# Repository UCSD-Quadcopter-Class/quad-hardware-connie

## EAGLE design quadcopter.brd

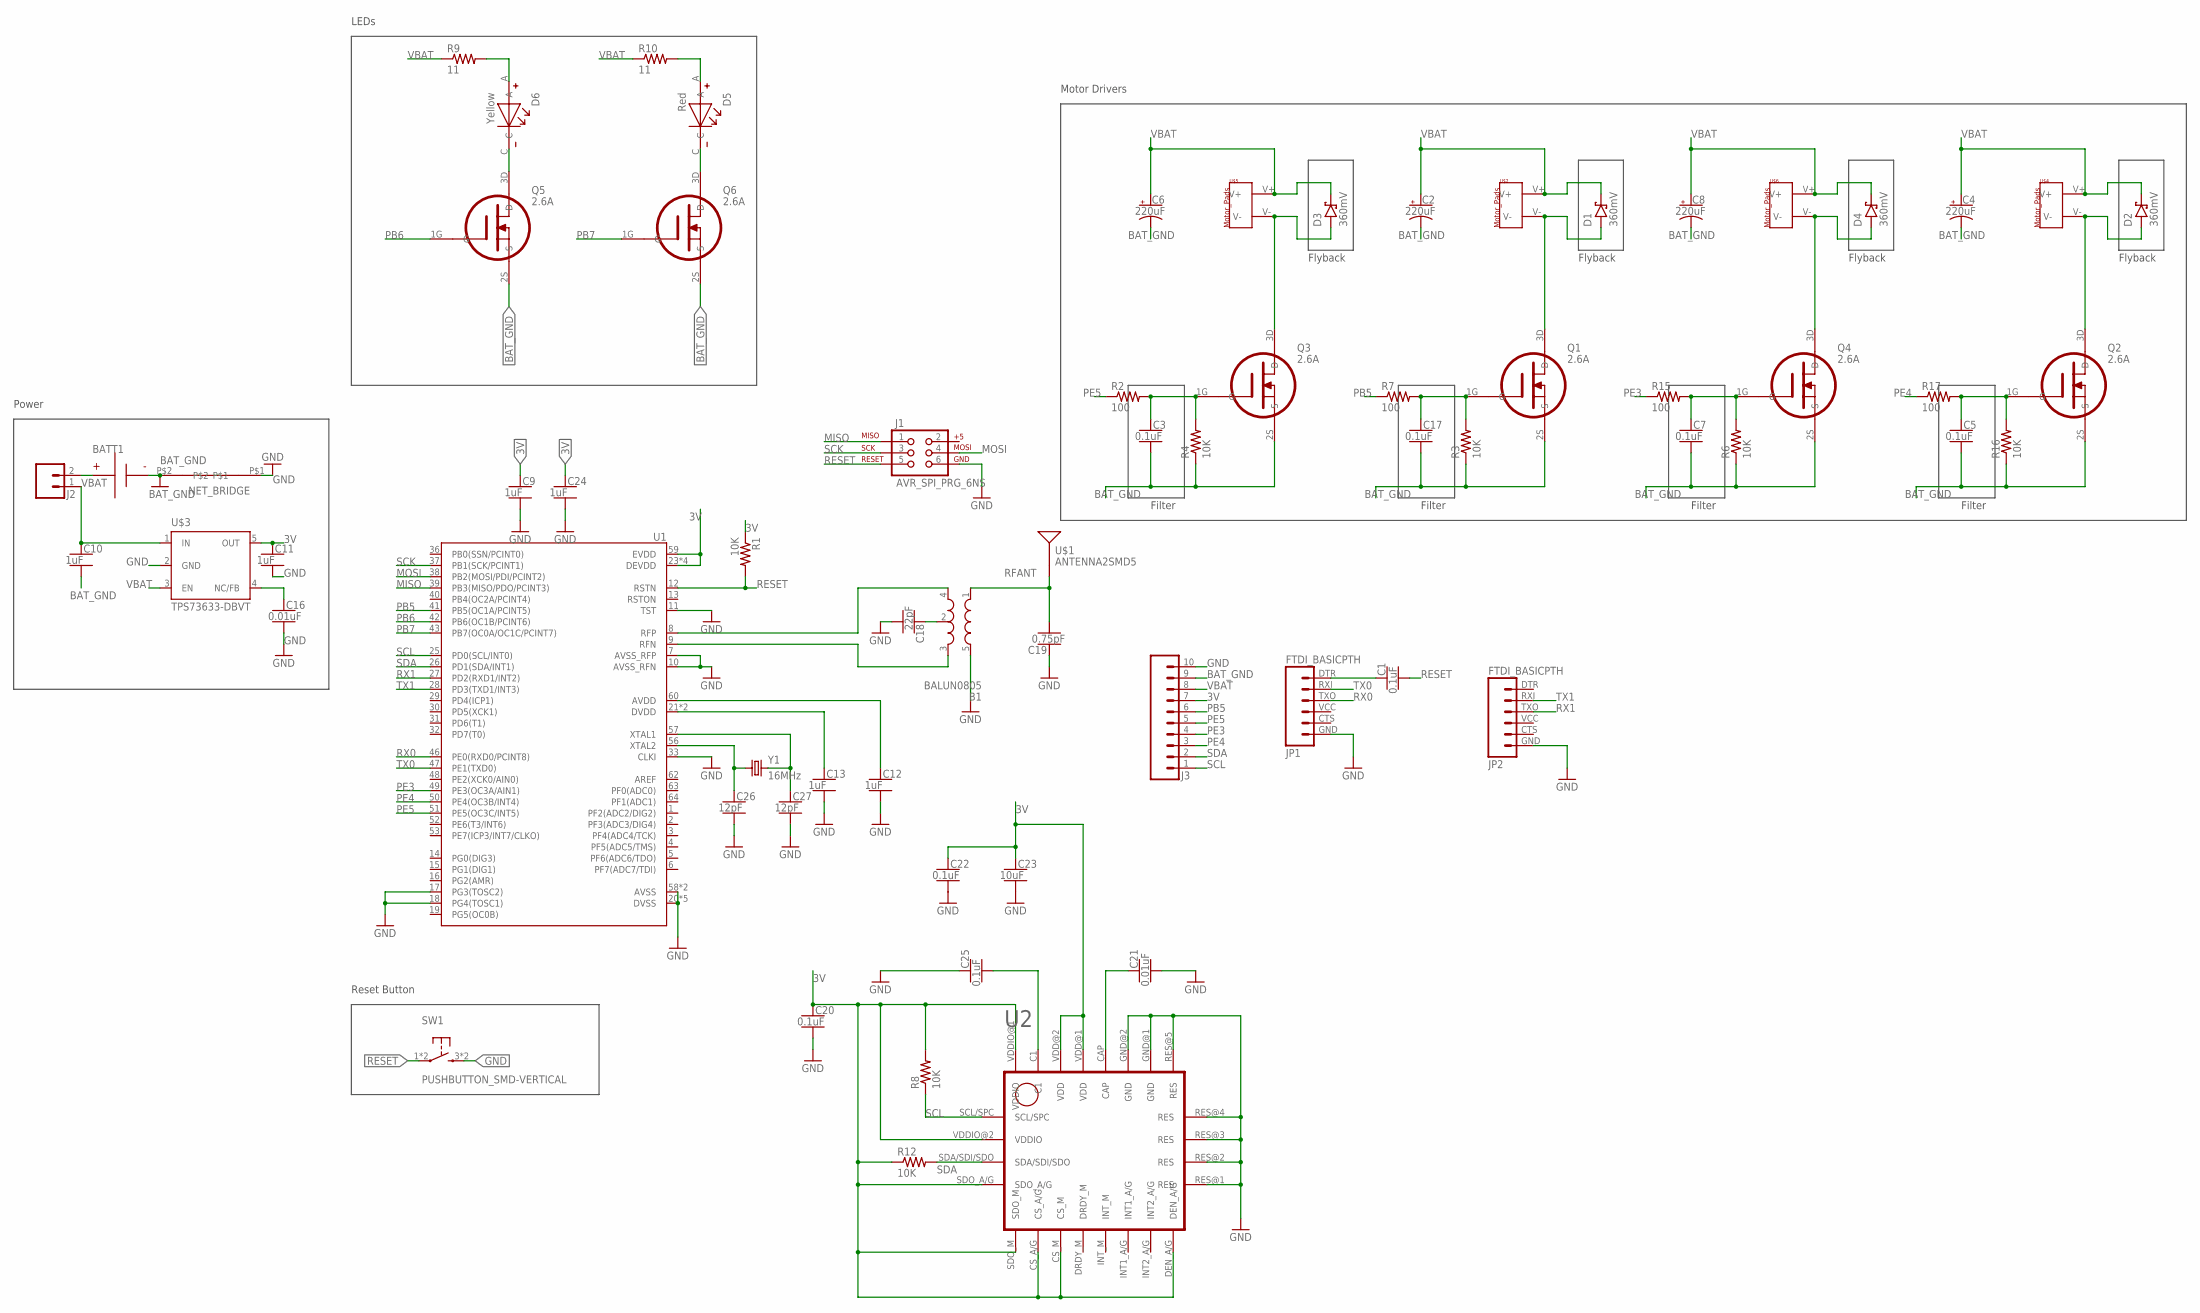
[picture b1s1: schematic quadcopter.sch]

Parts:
B1: BALUN0805; BALUN
BATT1: BATTERY-HUBSAN-W/HOLDER; BATTERY-W/HOLDER-380MAH-HUBSAN
C1: 0.1uF; CERAMIC_CAP_0805
C2, C4, C6, C8: 220uF; CAPMP7343X310_HS
C3, C5, C7, C17, C20, C22, C25: 0.1uF; CAPC2012X140_HS
C9, C10, C11, C12, C13, C24: 1uF; CAPC2012X140_HS
C16, C21: 0.01uF; CAPC2012X140_HS
C18: 22pF; CAPC2012X140_HS
C19: 0.75pF; CAPC2012X140_HS
C23: 10uF; CAPC2012X140_HS
C26, C27: 12pF; CAPC2012X140_HS
D1, D2, D3, D4: 360mV; SOD3716X135_HS
D5: Red; LED_VLMX51Z1AA
D6: Yellow; LED_VLMX51Z1AA
J1: AVR_SPI_PRG_6NS; 2X3-NS
J2: MALE_HEADER_2POS-2X1-0.1IN; MALE_HEADER_2X1_0.1IN
J3: SIP-10_TH-254X10; HDRV10W63P254_10X1_2540X254H838_HS
JP1, JP2: FTDI_BASICPTH; FTDI_BASIC
NET_BRIDGE: NET_BRIDGE
Q1, Q2, Q3, Q4, Q5, Q6: 2.6A; N_MOSFET_SI2302CDS_T1_E3
R1, R3, R4, R6, R8, R12, R16: 10K; RESC2012X60_HS
R2, R7, R15, R17: 100; RESC2012X60_HS
R9, R10: 11; RESC2012X60_HS
SW1: PUSHBUTTON_SMD-VERTICAL; TE_FSM8JSMA_HS
U1: ATMEGA128RFA1; QFN-64
U2: IMU_LSM9DS1TR
U$1: ANTENNA2SMD5; ANTENNA-CHIP5
U$2, U$4, U$5, U$6: MOTOR_PADS
U$3: TPS73633-DBVT; SOT23-DBV
Y1: 16MHz; CRYSTAL-SMD-5X3

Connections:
3V: C9.1, C11.1, C20.1, C22.1, C23.1, C24.1, J3.7, R1.1, R8.2, R12.1, U1.23 (DEVDD), U1.34 (DEVDD), U1.44 (DEVDD), U1.54 (DEVDD), U1.59 (EVDD), U2.CS_A/G, U2.CS_M, U2.DEN_A/G, U2.SDO_A/G, U2.SDO_M, U2.VDD@1 (VDD), U2.VDD@2 (VDD), U2.VDDIO@1 (VDDIO), U2.VDDIO@2 (VDDIO), U$3.5 (OUT)
BAT_GND: BATT1.- (N), C2.2 (-), C3.2, C4.2 (-), C5.2, C6.2 (-), C7.2, C8.2 (-), C10.2, C17.2, J3.9, NET_BRIDGE.P$2, Q1.2S (S), Q2.2S (S), Q3.2S (S), Q4.2S (S), Q5.2S (S), Q6.2S (S), R3.1, R4.1, R6.1, R16.1
FILTERED: C7.1, Q4.1G (G), R6.2, R15.2
GND: B1.5 (GND), C9.2, C11.2, C12.2, C13.2, C16.2, C18.2, C19.1, C20.2, C21.2, C22.2, C23.2, C24.2, C25.1, C26.2, C27.2, J1.6, J3.10, JP1.GND (6), JP2.GND (6), NET_BRIDGE.P$1, SW1.3 (2), SW1.4 (2), U1.7 (AVSS_RFP), U1.10 (AVSS_RFN), U1.11 (TST), U1.17 (PG3(TOSC2)), U1.18 (PG4(TOSC1)), U1.20 (DVSS), U1.24 (DVSS), U1.33 (CLKI), U1.35 (DVSS), U1.45 (DVSS), U1.55 (DVSS), U1.58 (AVSS), U1.61 (AVSS), U2.GND@1 (GND), U2.GND@2 (GND), U2.RES@1 (RES), U2.RES@2 (RES), U2.RES@3 (RES), U2.RES@4 (RES), U2.RES@5 (RES), U$3.2 (GND)
MISO: J1.1, U1.39 (PB3(MISO/PDO/PCINT3))
MOSI: J1.4, U1.38 (PB2(MOSI/PDI/PCINT2))
unnamed: C1.1, JP1.DTR (1)
unnamed: D6.C, Q5.3D (D)
unnamed: D6.A, R9.2
unnamed: D5.C, Q6.3D (D)
unnamed: C27.1, U1.57 (XTAL1), Y1.3 (2)
unnamed: D5.A, R10.2
unnamed: C12.1, U1.60 (AVDD)
unnamed: C13.1, U1.21 (DVDD), U1.22 (DVDD)
unnamed: C26.1, U1.56 (XTAL2), Y1.1
unnamed: C25.2, U2.C1
unnamed: D1.A, Q1.3D (D), U$2.V-
unnamed: C21.1, U2.CAP
unnamed: B1.4 (OUT1), U1.8 (RFP)
unnamed: B1.3 (OUT2), U1.9 (RFN)
unnamed: BATT1.+, J2.2
unnamed: D3.A, Q3.3D (D), U$5.V-
unnamed: B1.2 (GND), C18.1
unnamed: D4.A, Q4.3D (D), U$6.V-
unnamed: D2.A, Q2.3D (D), U$4.V-
unnamed: C3.1, Q3.1G (G), R2.2, R4.2
unnamed: C16.1, U$3.4 (NC/FB)
unnamed: C17.1, Q1.1G (G), R3.2, R7.2
unnamed: C5.1, Q2.1G (G), R16.2, R17.2
PB5: J3.6, R7.1, U1.41 (PB5(OC1A/PCINT5))
PB6: Q5.1G (G), U1.42 (PB6(OC1B/PCINT6))
PB7: Q6.1G (G), U1.43 (PB7(OC0A/OC1C/PCINT7))
PE3: J3.4, R15.1, U1.49 (PE3(OC3A/AIN1))
PE4: J3.3, R17.1, U1.50 (PE4(OC3B/INT4))
PE5: J3.5, R2.1, U1.51 (PE5(OC3C/INT5))
RESET: C1.2, J1.5, R1.2, SW1.1, SW1.2 (1), U1.12 (RSTN)
RFANT: B1.1 (IN), C19.2, U$1.FEED
RX0: JP1.TXO (3), U1.46 (PE0(RXD0/PCINT8))
RX1: JP2.TXO (3), U1.27 (PD2(RXD1/INT2))
SCK: J1.3, U1.37 (PB1(SCK/PCINT1))
SCL: J3.1, R8.1, U1.25 (PD0(SCL/INT0)), U2.SCL/SPC
SDA: J3.2, R12.2, U1.26 (PD1(SDA/INT1)), U2.SDA/SDI/SDO
TX0: JP1.RXI (2), U1.47 (PE1(TXD0))
TX1: JP2.RXI (2), U1.28 (PD3(TXD1/INT3))
VBAT: C2.1 (+), C4.1 (+), C6.1 (+), C8.1 (+), C10.1, D1.C, D2.C, D3.C, D4.C, J2.1, J3.8, R9.1, R10.1, U$2.V+, U$3.1 (IN), U$3.3 (EN), U$4.V+, U$5.V+, U$6.V+

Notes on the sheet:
Flyback
Filter
Reset Button
LEDs
Motor Drivers
Power

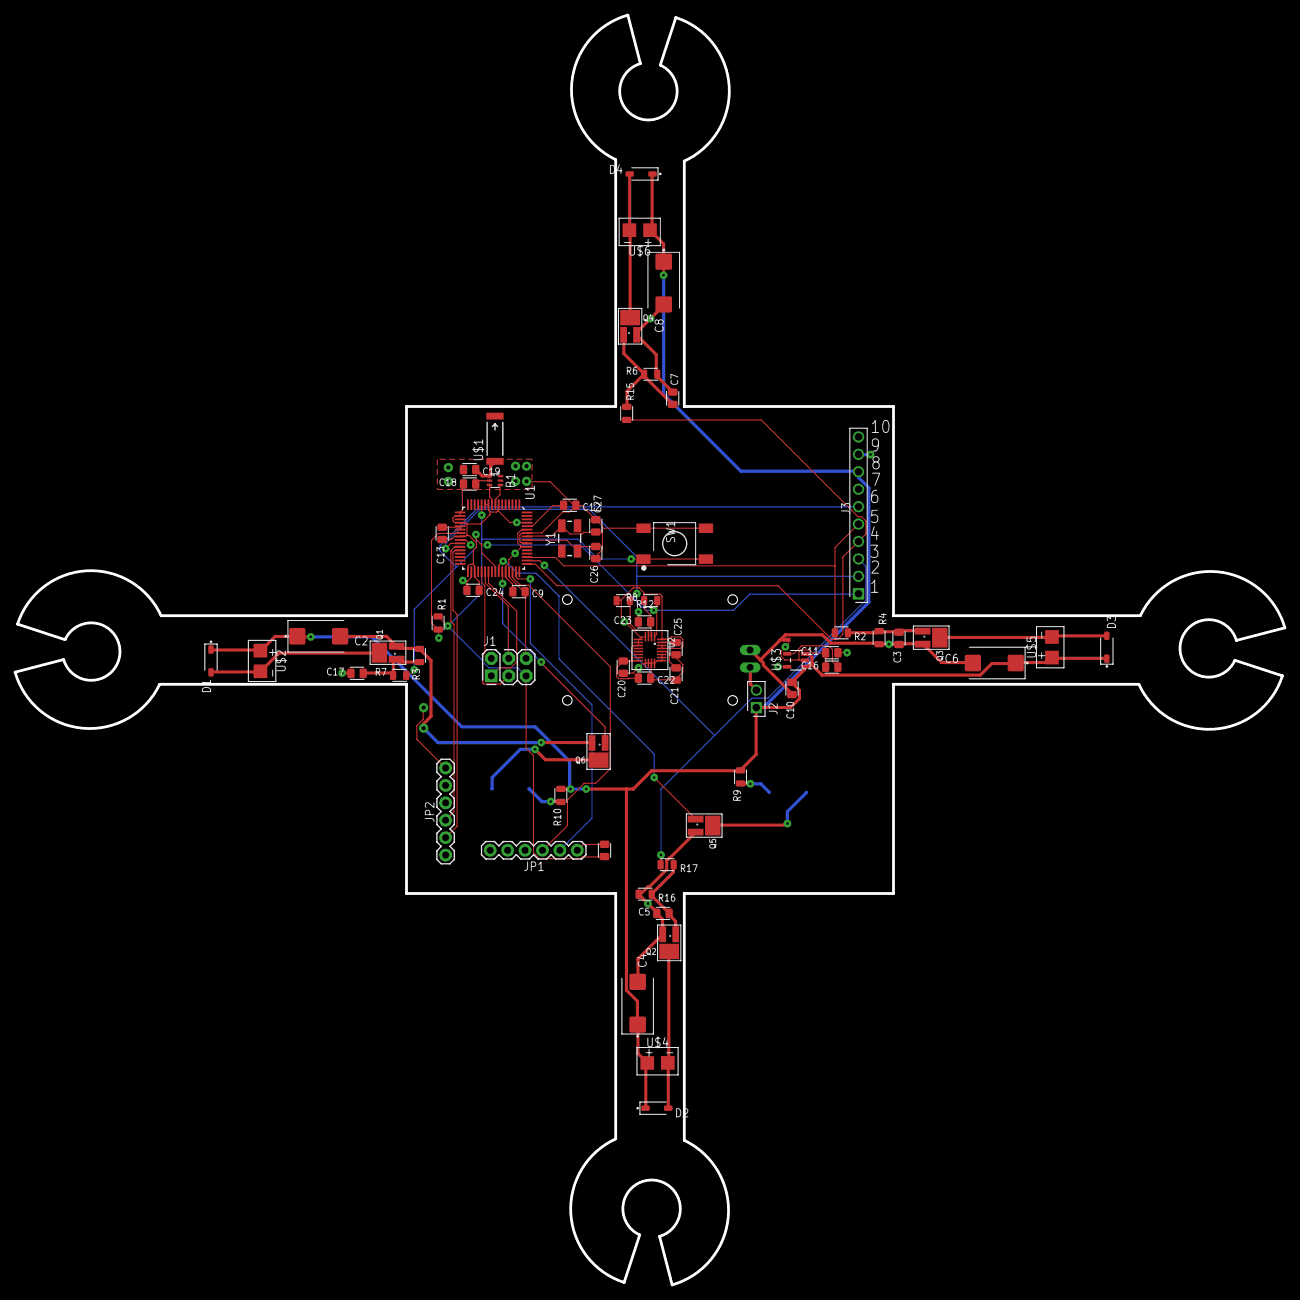
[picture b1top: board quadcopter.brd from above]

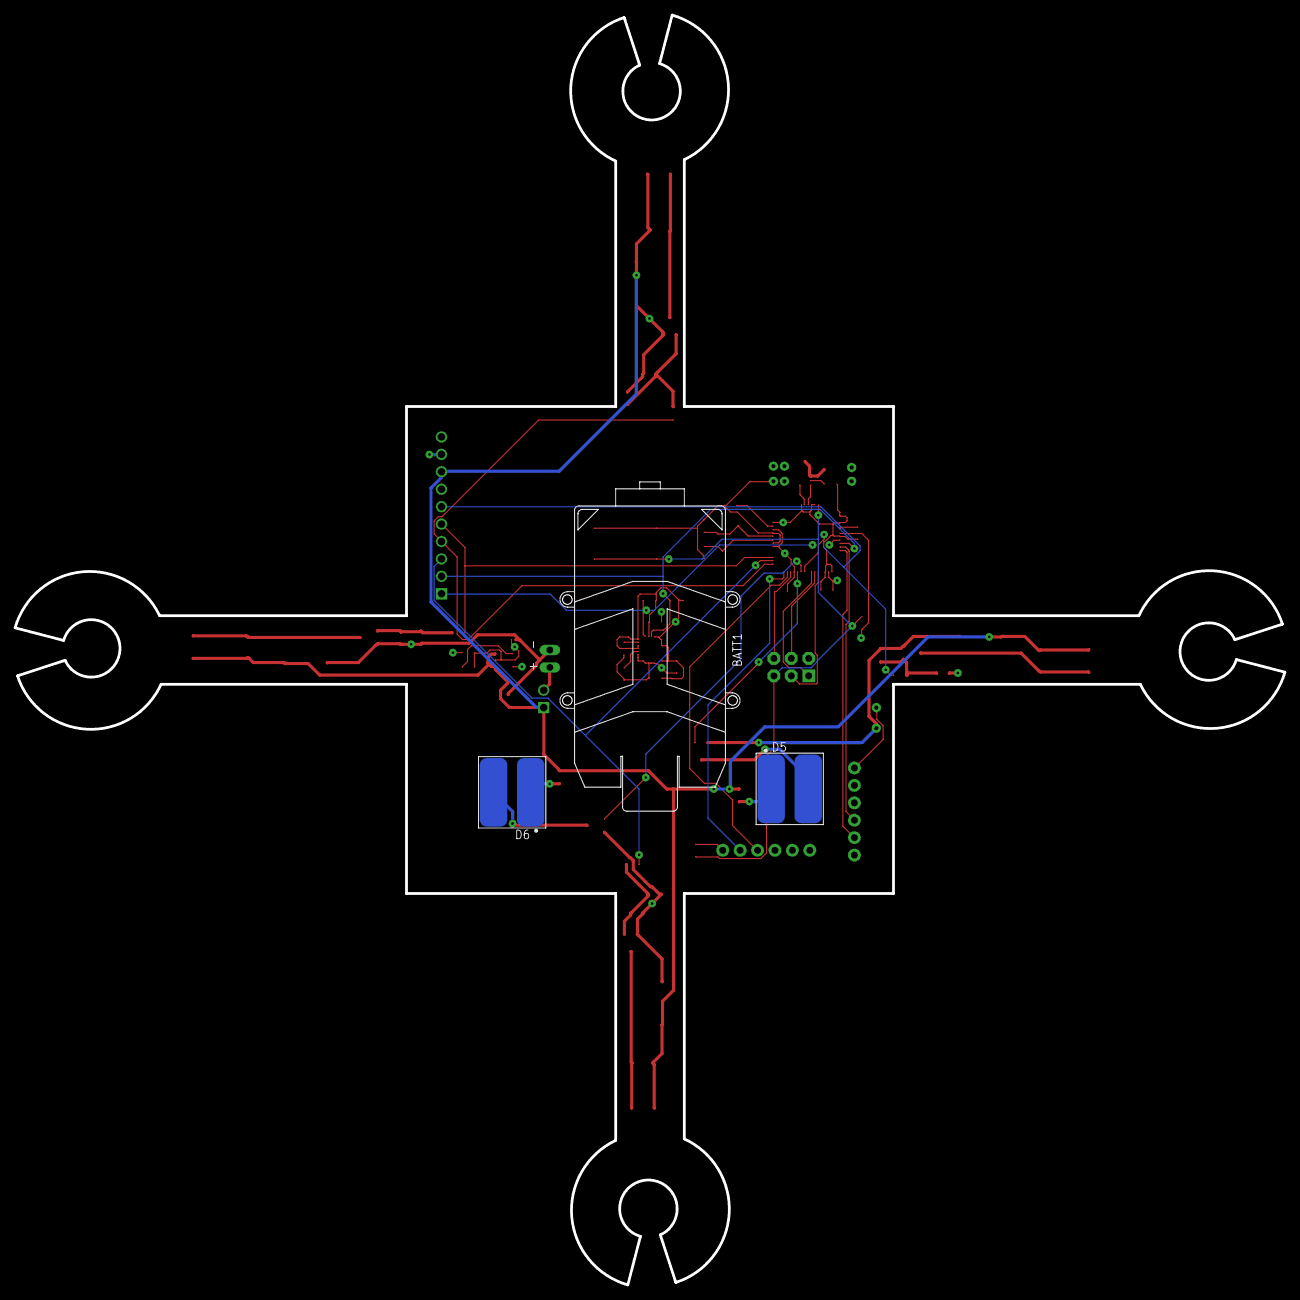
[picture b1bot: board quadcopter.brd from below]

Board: 4 copper layers, 185.1 x 185.1 mm, 68 parts (3 on the bottom side), 45 nets.

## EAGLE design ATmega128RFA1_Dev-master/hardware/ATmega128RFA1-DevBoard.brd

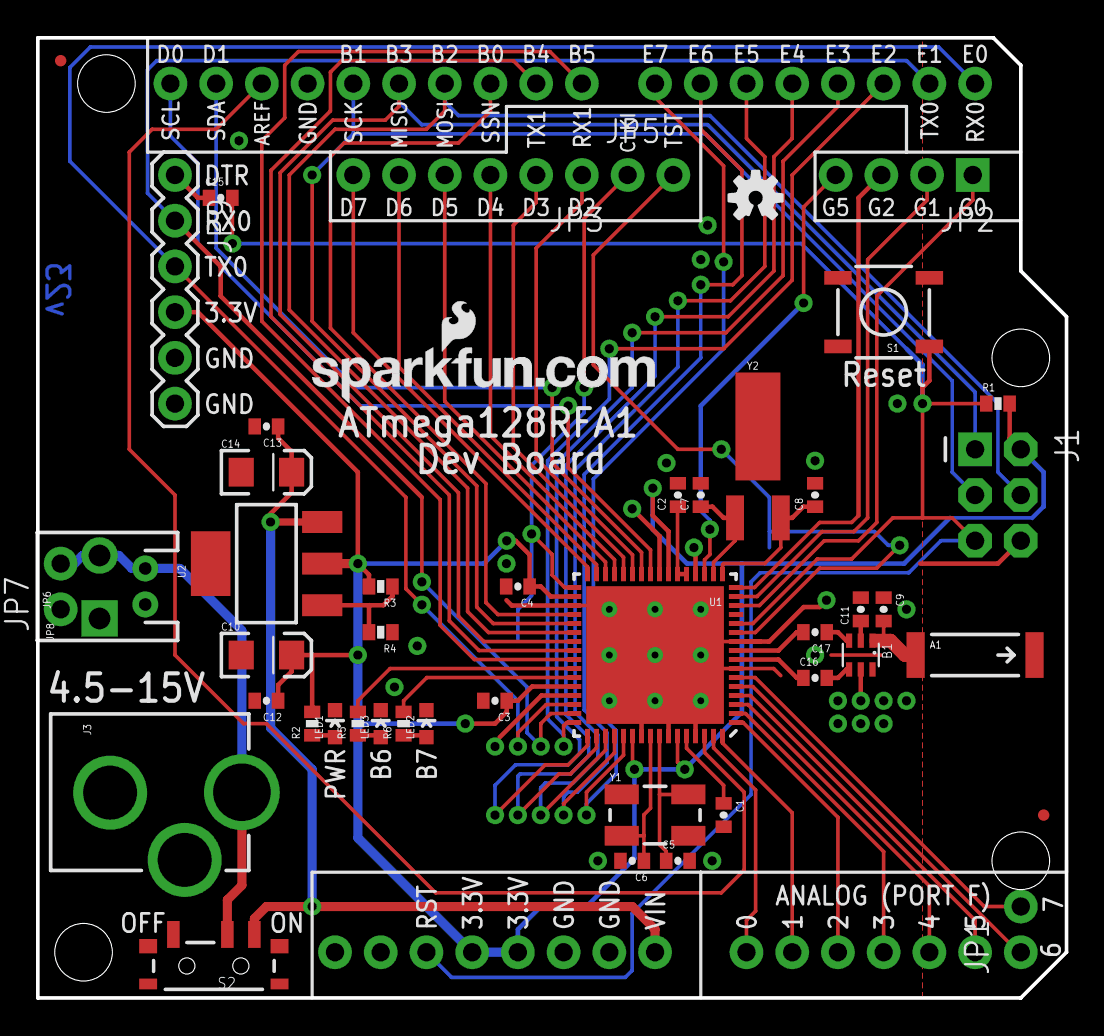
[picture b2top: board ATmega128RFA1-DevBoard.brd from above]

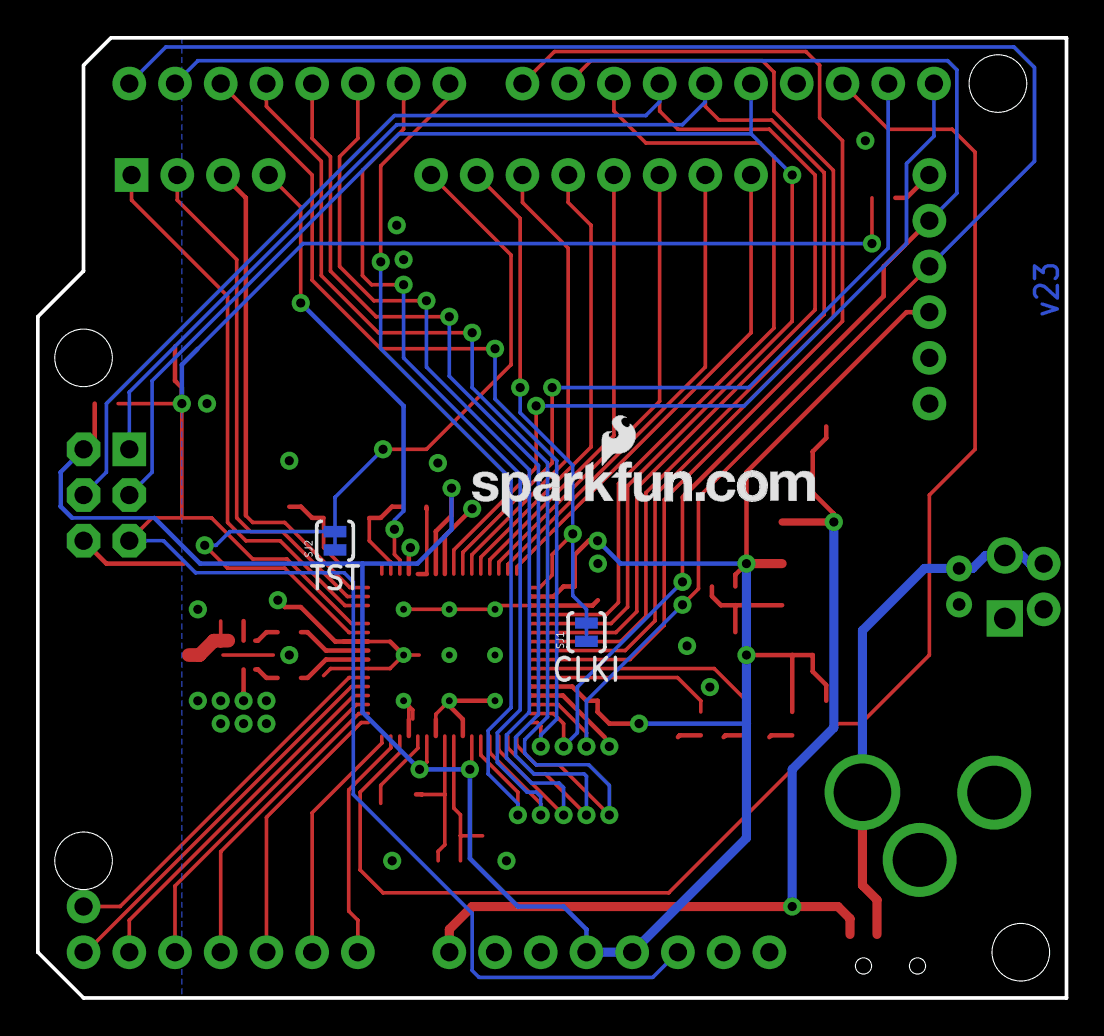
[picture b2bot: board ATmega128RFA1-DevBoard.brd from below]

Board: 2 copper layers, 57.1 x 53.3 mm, 52 parts (3 on the bottom side), 61 nets.

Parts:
A1: ANTENNA2SMD5; ANTENNA-CHIP5
B1: 748421245; BALUN
C1, C2, C3, C4, C12: 1uF; 0402-CAP
C5, C6, C7, C8: 12pF; 0402-CAP
C9: 0.75pF; 0402-CAP
C10, C14: 10uF; EIA3216
C11: 22pF; 0402-CAP
C13, C15: 0.1uF; 0402-CAP
C16, C17: JUMP; 0402-CAP
FID1, FID2: FIDUCIALUFIDUCIAL; MICRO-FIDUCIAL
J1: ISP; 2X3-NS
J2: ARDUINO_UNO_R3
J3: POWER_JACKPTH_LOCK; POWER_JACK_PTH_LOCK
JP1, JP5, JP7: 1X02_NO_SILK
JP2: 1X04_NO_SILK
JP3: 1X06_NS
JP4, JP10: LOGO-SFENEW; SFE-NEW-WEBLOGO
JP6: JST-2-PTH
JP8: SCREWTERMINAL-3.5MM-2-NS
JP9: FTDI; FTDI_BASIC
LED1: RED; LED-0603
LED2, LED3: GREEN; LED-0603
R1: 10k; 0402-RES
R2: 1k; 0402-RES
R3: 240; 0402-RES
R4: 390; 0402-RES
R5, R6: 330; 0402-RES
S1: TACTILE_SWITCH_SMD
S2: SWITCH-SPST-SMD-A
SJ1, SJ2: SJ_2S-TRACE
U1: ATMEGA128RFA1; QFN-64
U2: LM1117; SOT223
U$1: OSHW-LOGOS; OSHW-LOGO-S
Y1: 16MHz; CRYSTAL-SMD-5X3
Y2: 32.768kHz; CRYSTAL-32KHZ-SMD

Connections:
3.3V: C3.1, C4.1, C10.A, C12.1, J1.2, J2.3.3V, J2.5V, JP9.VCC, R1.2, R2.2, R3.2, U1.23, U1.34, U1.44, U1.54, U1.59, U2.2
A0: J2.A0, U1.63
A1: J2.A1, U1.64
A2: J2.A2, U1.1
A3: J2.A3, U1.2
A4: J2.A4, U1.3
A5: J2.A5, U1.4
A6: JP1.1, U1.5
A7: JP1.2, U1.6
AREF: J2.AREF, U1.62
AVDD: C1.1, U1.60
CLKI: JP5.1, SJ1.2, U1.33
DTR: C15.1, JP9.DTR
DVDD: C2.1, U1.21, U1.22
FB: R3.1, R4.2, U2.1
GND: B1.5, C1.2, C2.2, C3.2, C4.2, C5.2, C6.2, C7.2, C8.2, C9.1, C10.C, C11.2, C12.2, C13.2, C14.C, J1.6, J2.GND@0, J2.GND@1, J2.GND@2, J3.GND, J3.GNDBREAK, JP6.1, JP7.1, JP8.1, JP9.GND, LED1.C, LED2.C, LED3.C, R4.1, S1.3, SJ1.1, SJ2.1, U1.7, U1.10, U1.20, U1.24, U1.35, U1.45, U1.55, U1.58, U1.61, U1.65
MISO: J1.1, J2.D12, U1.39
MOSI: J1.4, J2.D11, U1.38
unnamed: LED1.A, R2.1
unnamed: C5.1, U1.57, Y1.3
unnamed: C6.1, U1.56, Y1.1
unnamed: C7.1, U1.18, Y2.X1
unnamed: C8.1, U1.17, Y2.X2
unnamed: B1.2, C11.1
unnamed: LED3.A, R5.1
unnamed: J3.PWR, JP6.2, JP7.2, JP8.2, S2.2
unnamed: B1.4, C16.2
unnamed: B1.3, C17.1
unnamed: LED2.A, R6.1
PB4: J2.D9, U1.40
PB5: J2.D8, U1.41
PB6: R5.2, U1.42
PB7: R6.2, U1.43
PD4: JP3.3, U1.29
PD5: JP3.4, U1.30
PD6: JP3.5, U1.31
PD7: JP3.6, U1.32
PE2: J2.D2, U1.48
PE3: J2.D3, U1.49
PE4: J2.D4, U1.50
PE5: J2.D5, U1.51
PE6: J2.D6, U1.52
PE7: J2.D7, U1.53
PG0: JP2.1, U1.14
PG1: JP2.2, U1.15
PG2: JP2.3, U1.16
PG5: JP2.4, U1.19
RESET: C15.2, J1.5, J2.RES, R1.1, S1.1, U1.12
RFANT: A1.FEED, B1.1, C9.2
RFN: C17.2, U1.9
RFP: C16.1, U1.8
RX0: J2.RX, JP9.TXO, U1.46
RX1: JP3.1, U1.27
SCK: J1.3, J2.D13, U1.37
SCL: J2.SCL, U1.25
SDA: J2.SDA, U1.26
SSN: J2.D10, U1.36
TST: JP5.2, SJ2.2, U1.11
TX0: J2.TX, JP9.RXI, U1.47
TX1: JP3.2, U1.28
VCC: C13.1, C14.A, J2.VIN, S2.1, U2.3

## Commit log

2017-04-15 Adding Connie's quadparts
2017-04-18 added ATmega design files, parts list, jason's library
2017-04-18 started
2017-04-18 updated quadcopter schematic
2017-04-18 finished, for the most part, microcontroller section
2017-04-19 Sort of finished motor driver sch
2017-04-19 added stuff
2017-04-19 added more stuff
2017-04-20 added LED library
2017-04-20 LED datasheets added
2017-04-20 tiny changes
2017-04-20 added led_notes
2017-04-20 added current-limiting resistors
2017-04-20 random non-changes
2017-04-25 added design reviews
2017-04-25 changes to schematic and connie lbr
2017-04-25 Finished changes from design review in quadparts.sch
2017-04-25 Corrected IMU package in connie.lbr
2017-04-25 added tPlace outline to IMU package
2017-04-27 instructior review of original schematic
2017-04-27 fixed imu cs lines and added pullup resistor
2017-04-27 Fixed most things from Professor's notes in schematic
2017-04-27 stuff
2017-04-27 IMU is correct now I think?
2017-04-27 fixed mosfet
2017-04-28 fixed some schematic stuff
2017-04-28 made lots of semicircles
2017-04-29 Worked on board a bit, got two rough draft outlines for board?
2017-04-30 tried some stuff on board
2017-04-30 cleanup
2017-05-01 added board stuff
2017-05-01 Restricting the Autorouter- setting trace widths - done?
2017-05-02 did the imu protection, voltage regulator, breakout header stuff:
2017-05-02 polygons may have fallen apart
2017-05-02 no more airwires!
2017-05-04 added design review stuff
2017-05-04 other design review added
2017-05-04 Some changes to brd
2017-05-07 improved brd..?
2017-05-10 fixed drc errors and routed 98%
2017-05-10 Wired up
2017-05-11 Tiny change
2017-05-11 Fixed stop mask errors generated by autorouter
2017-05-11 added faraday cage around antenna driver
2017-05-11 swanson review
2017-05-14 more schematic comments from swanson
2017-05-15 Some changes based on design reviews
2017-05-15 fixed sch errors
2017-05-16 Fixed board errors
2017-05-16 Board ready for final review
2017-05-17 Board comments from swanson
2017-05-18 Fixed new board errors
2017-05-19 more board fixes

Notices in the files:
parts and their libraries:
SparkFun-DigitalIC: Licensing: CC v3.0 Share-Alike You are welcome to use this library for commercial purposes.
